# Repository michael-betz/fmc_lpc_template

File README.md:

# fmc_lpc_template

Kicad template for an FPGA Mezzanine Card with Low Pin Count connector (FMC-LPC).

Needs Kicad 5.99.

Ordered by JLCPCB and confirmed to fit.

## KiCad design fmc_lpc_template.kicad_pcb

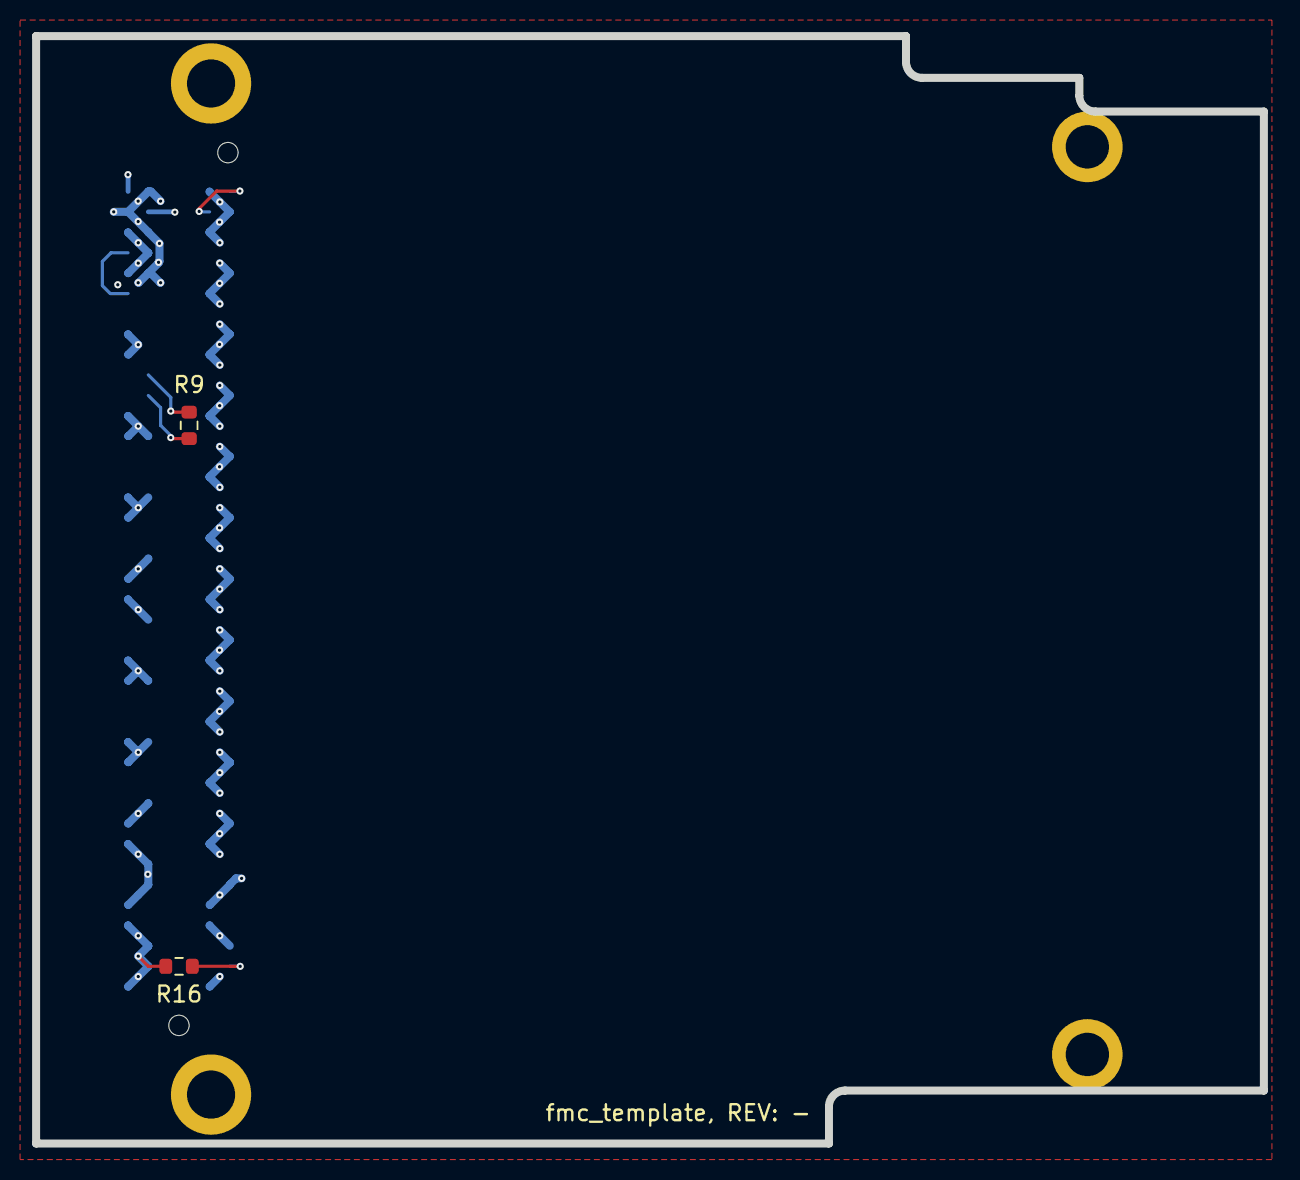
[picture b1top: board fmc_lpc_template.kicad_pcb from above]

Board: 4 copper layers, 76.5 x 69.0 mm, 5 parts (1 on the bottom side), 7 nets.

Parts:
B1, B2: PLATED_HOLE2.7_PAD5.0; MTG270_500
J5: ASP-134604-01; Samtec_FMC_ASP-134604-01_4x40_Vertical
R9, R16: 100R; R_0603_1608Metric

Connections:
+3V3: J5.C39, J5.D36, J5.D38, J5.D40
+12V: J5.C35, J5.C37
/FMC/PRSNT_M2C_L: J5.H2, R16.2
/FMC/TDI: J5.D30, R9.2
/FMC/TDO: J5.D31, R9.1
GND: J5.C1, J5.C4, J5.C5, J5.C8, J5.C9, J5.C12, J5.C13, J5.C16, J5.C17, J5.C20, J5.C21, J5.C24, J5.C25, J5.C28, J5.C29, J5.C32, J5.C33, J5.C36, J5.C38, J5.C40, J5.D2, J5.D3, J5.D6, J5.D7, J5.D10, J5.D13, J5.D16, J5.D19, J5.D22, J5.D25, J5.D28, J5.D37, J5.D39, J5.G1, J5.G4, J5.G5, J5.G8, J5.G11, J5.G14, J5.G17, J5.G20, J5.G23, J5.G26, J5.G29, J5.G32, J5.G35, J5.G38, J5.G40, J5.H3, J5.H6, J5.H9, J5.H12, J5.H15, J5.H18, J5.H21, J5.H24, J5.H27, J5.H30, J5.H33, J5.H36, J5.H39, R16.1
VDDA: J5.G39, J5.H40

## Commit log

2021-08-28 update pcb from schematic
    * looks like it re-numbered the nets
    * no change on the pcb
2021-08-28 add 3D model and render
